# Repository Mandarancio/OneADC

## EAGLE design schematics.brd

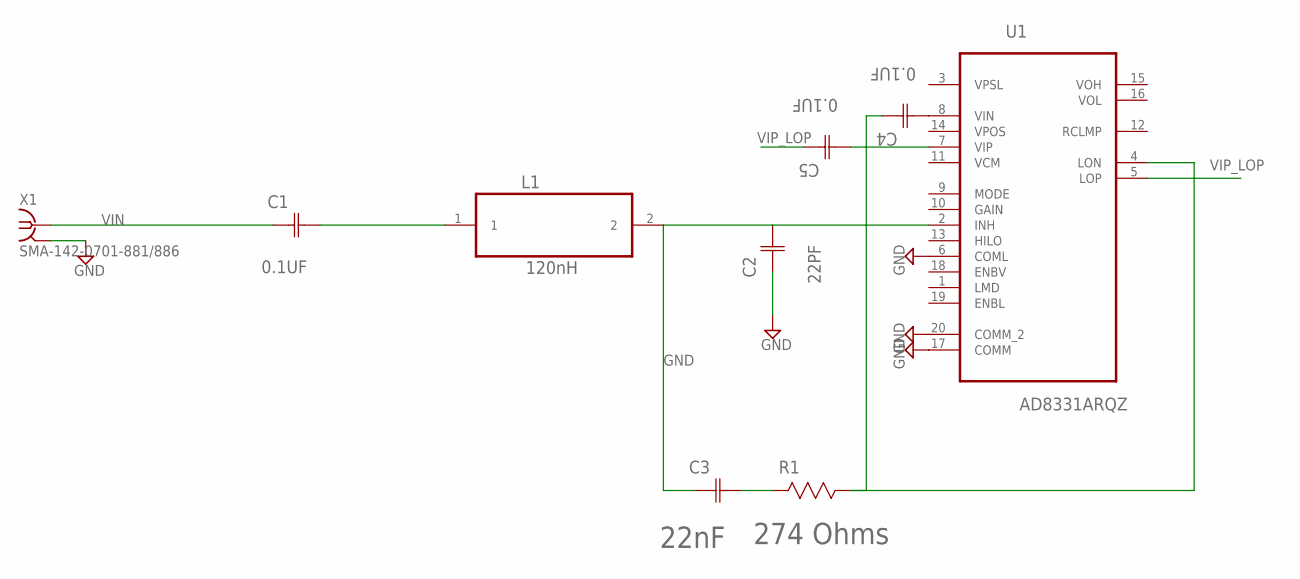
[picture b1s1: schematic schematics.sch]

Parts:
C1, C4, C5: 0.1UF; CAPC3216X94N
C2: 22PF; CAPC3216X94N
C3: 22nF; CAPC2013X88N
L1: 120nH; INDC2317X140N
R1: 274 Ohms; RESC3216X71N
U1: AD8331ARQZ; SOP64P600X165-20N
X1: SMA-142-0701-881/886; J502-ND-142-0701-881/886

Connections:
GND: C2.1 (C1), U1.6 (COML), U1.17 (COMM), U1.20 (COMM_2), X1.G@1 (2), X1.G@2 (2), X1.G@3 (2), X1.G@4 (2)
unnamed: C1.2 (C2), L1.1
unnamed: C2.2 (C2), C3.1 (C1), L1.2, U1.2 (INH)
unnamed: C3.2 (C2), R1.2
unnamed: C4.1 (C1), R1.1, U1.4 (LON)
unnamed: C4.2 (C2), U1.8 (VIN)
unnamed: C5.2 (C2), U1.7 (VIP)
VIN: C1.1 (C1), X1.1
VIP_LOP: C5.1 (C1), U1.5 (LOP)
VPOS: U1.14 (VPOS)
VPSL: U1.3 (VPSL)

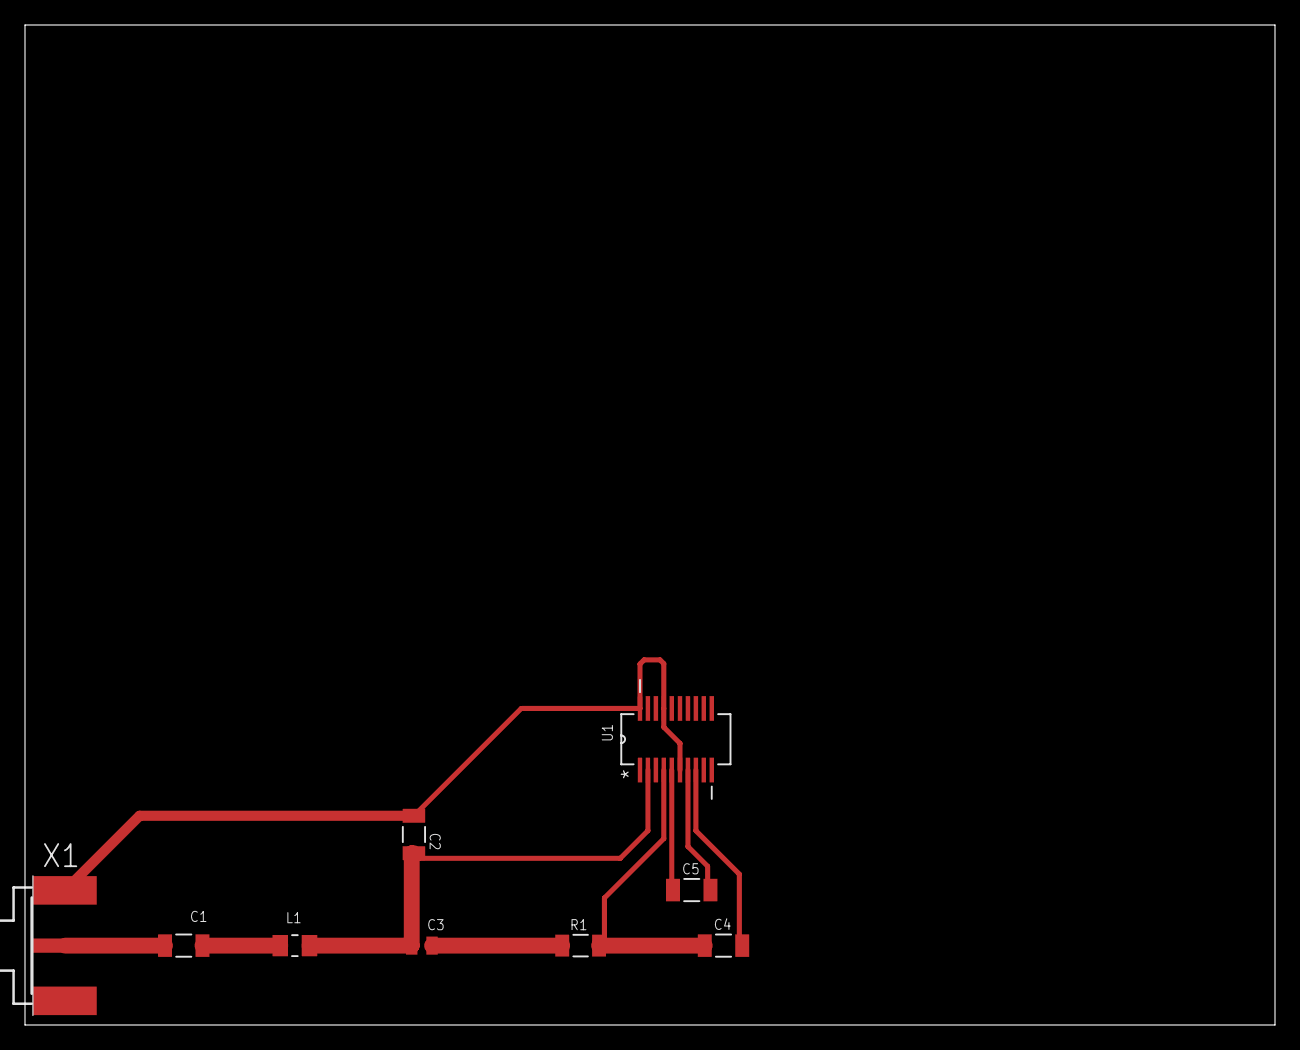
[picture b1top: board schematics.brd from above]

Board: 2 copper layers, 100.0 x 80.0 mm, 9 parts (0 on the bottom side), 9 nets.

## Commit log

2015-12-02 Test commit
2015-12-03 Added files...
2015-12-03 Removed test files
